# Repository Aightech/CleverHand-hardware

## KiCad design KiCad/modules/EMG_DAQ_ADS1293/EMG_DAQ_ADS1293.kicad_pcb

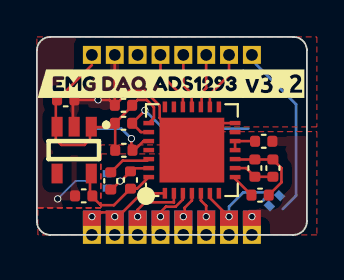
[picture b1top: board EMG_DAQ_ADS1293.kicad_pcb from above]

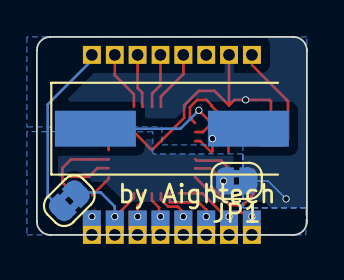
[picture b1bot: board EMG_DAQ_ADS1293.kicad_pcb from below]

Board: 4 copper layers, 15.0 x 11.0 mm, 34 parts (3 on the bottom side), 22 nets.

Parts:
C1, C5, C7: 100nF; C_0402_1005Metric
C2, C8, C9: 1uF; C_0402_1005Metric
C3, C4: 22pF; C_0402_1005Metric
C6: 1nF; C_0402_1005Metric
J1, J2, J3, J4, J5, J6, J7, J8, J9, J10, J11, J12, J13, J14, J15, J16: Conn_01x01_Pin; PinHeader_1x01_P1.27mm_Vertical
JP1, JP2: SolderJumper_2_Bridged; SolderJumper-2_P1.3mm_Bridged2Bar_RoundedPad1.0x1.5mm
R1: 10K; C_0402_1005Metric
R2: 10M; C_0402_1005Metric
U1: ADS1293CISQE-NOPB; ADS1293CISQE
U2: AP2112K-3.3TRG1; SOT-25-5_L2.9-W1.6-P0.95-LS2.8-BL
Y1: Crystal; Crystal_SMD_HC49-SD
kibuzzard-66CB9060: G***; kibuzzard-66CB9060
kibuzzard-658D7E24: G***; kibuzzard-658D7E24

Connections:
+3.3V: C3.1, C4.1, C5.1, C9.1, J13.1, U1.22 (VDDIO), U2.1 (VIN), U2.3 (EN)
+3.3VA: C1.1, C8.1, U1.28 (VDD), U2.5 (VOUT)
/CMOUT: R1.2, U1.8 (CMOUT)
/CSB: J12.1, U1.16 (CSB)
/PICO: J10.1, U1.18 (SDI)
/POCI: J9.1, U1.19 (SDO)
/RLDINV: C6.1, R1.1, R2.1, U1.10 (RLDINV)
/RLDOUT: C6.2, R2.2, U1.9 (RLDOUT)
/RLDREF: C7.1, U1.11 (RLDIN), U1.12 (RLDREF)
/SCLK: J11.1, U1.17 (SCLK)
/cvref: C2.1, U1.26 (CVREF)
/extRef: J7.1, JP2.1 (A)
/in1: J2.1, J3.1, U1.1 (IN1)
/in2: J4.1, U1.2 (IN2)
/in3: J5.1, U1.3 (IN3)
/in4: J6.1, U1.4 (IN4)
/in5: J8.1, U1.5 (IN5)
/in6: J15.1, JP2.2 (B), U1.6 (IN6)
GND: C5.2, C8.2, C9.2, J14.1, JP1.1 (A), U1.14 (VSSIO), U1.29 (EPAD), U2.2 (GND)
GNDA: C1.2, C2.2, C7.2, J16.1, JP1.2 (B), U1.27 (VSS)
XTAL1: C4.2, U1.23 (XTAL1), Y1.1
XTAL2: C3.2, U1.24 (XTAL2), Y1.2

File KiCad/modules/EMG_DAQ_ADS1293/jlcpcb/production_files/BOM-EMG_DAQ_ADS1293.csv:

Comment,Designator,Footprint,LCSC
10M,R2,C_0402_1005Metric,C102764
1nF,C6,C_0402_1005Metric,C1523
100nF,"C1,C5,C7",C_0402_1005Metric,C1525
22pF,"C3,C4",C_0402_1005Metric,C1555
ADS1293CISQE-NOPB,U1,ADS1293CISQE,C181260
10K,R1,C_0402_1005Metric,C25744
AP2112K-3.3TRG1,U2,SOT-25-5_L2.9-W1.6-P0.95-LS2.8-BL,C51118
1uF,"C2,C8,C9",C_0402_1005Metric,C52923
Crystal,Y1,Crystal_SMD_HC49-SD,C74858
Conn_01x01_Pin,J1,PinHeader_1x01_P1.27mm_Vertical,
Conn_01x01_Pin,J9,PinHeader_1x01_P1.27mm_Vertical,
Conn_01x01_Pin,J7,PinHeader_1x01_P1.27mm_Vertical,
Conn_01x01_Pin,J10,PinHeader_1x01_P1.27mm_Vertical,
Conn_01x01_Pin,J14,PinHeader_1x01_P1.27mm_Vertical,
Conn_01x01_Pin,J12,PinHeader_1x01_P1.27mm_Vertical,
Conn_01x01_Pin,J11,PinHeader_1x01_P1.27mm_Vertical,
Conn_01x01_Pin,J13,PinHeader_1x01_P1.27mm_Vertical,
SolderJumper_2_Bridged,JP2,SolderJumper-2_P1.3mm_Bridged2Bar_RoundedPad1.0x1.5mm,
SolderJumper_2_Bridged,JP1,SolderJumper-2_P1.3mm_Bridged2Bar_RoundedPad1.0x1.5mm,

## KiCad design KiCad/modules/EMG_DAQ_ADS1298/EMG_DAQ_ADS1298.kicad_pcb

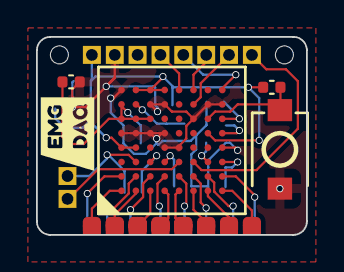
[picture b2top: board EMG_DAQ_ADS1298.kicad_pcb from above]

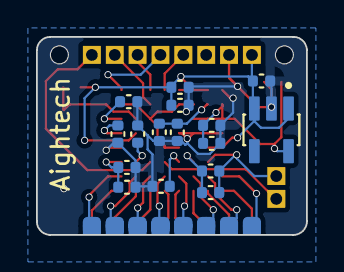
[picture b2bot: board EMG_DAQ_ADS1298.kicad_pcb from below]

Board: 4 copper layers, 15.0 x 11.0 mm, 47 parts (24 on the bottom side), 34 nets.

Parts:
C1, C2, C3, C5, C11, C12: 1uF; C_0402_1005Metric
C4, C6, C9, C14: 100nF; C_0402_1005Metric
C7: 1.5nF; C_0402_1005Metric
C8, C13: 10uF; C_0402_1005Metric
C10: 1nF; C_0402_1005Metric
C15: 22uF; C_0402_1005Metric
J1, J2, J3, J4, J5, J6, J7, J8, J25, J26: Conn_01x01_Pin; PinHeader_1x01_P1.27mm_Vertical
J9, J10, J11, J12, J13, J14, J15, J16, J17, J18, J19, J20, J21, J22, J23, J24: Conn_01x01_Pin; SolderWirePad_1x01_SMD_1x2mm
R1: 1M; C_0402_1005Metric
R2: 10K; C_0402_1005Metric
SW1: TS-1088R-02026; SW-SMD_L3.9-W3.0-P4.45
U1: AP2112K-3.3TRG1; SOT95P285X140-5N
U2: ADS1298CZXGT; NFBGA-64_L8.0-W8.0-R8-C8-P0.80-TL
kibuzzard-6569F40D: G***; kibuzzard-6569F40D

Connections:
+3.3V: C1.1, C3.2, C4.2, J1.1, R2.2, U1.1 (VIN), U1.3 (EN), U2.A4 (AVDD), U2.B4 (AVDD), U2.B8 (CLKSEL), U2.C8 (DVDD), U2.D8 (DVDD), U2.G5 (~PWDN)
+3.3VA: C2.1, C8.1, C9.1, U1.5 (VOUT), U2.A6 (AVDD), U2.A7 (AVDD1), U2.B6 (AVDD), U2.C6 (AVDD)
/BIAS_INV: C7.2, R1.1, U2.C3 (RLDINV)
/BIAS_OUT: C7.1, J26.1, R1.2, U2.B3 (RLDOUT)
/CSB: J7.1, U2.F7 (CS)
/MISO: J4.1, U2.E8 (DOUT)
/MOSI: J5.1, U2.H8 (DIN)
/RESET: R2.1, SW1.1, U2.G6 (~RESET)
/Refp: J25.1, U2.E3 (TESTP_PACE_OUT1)
/SCLK: J6.1, U2.F8 (SCLK)
/VCAP1: C15.1, U2.H5 (VCAP1)
/VCAP2: C12.1, U2.H6 (VCAP2)
/VCAP3: C5.1, C6.1, U2.B7 (VCAP3)
/VCAP4: C11.1, U2.G3 (VCAP4)
/VREFP: C13.1, C14.1, U2.H3 (VREFP)
/WCT: C10.1, U2.D3 (WCT)
/extRef: J8.1, U2.F3 (TESTN_PACE_OUT2)
/in1+: J16.1, U2.H1 (IN1P)
/in1-: J24.1, U2.H2 (IN1N)
/in2+: J15.1, U2.G1 (IN2P)
/in2-: J23.1, U2.G2 (IN2N)
/in3+: J14.1, U2.F1 (IN3P)
/in3-: J22.1, U2.F2 (IN3N)
/in4+: J13.1, U2.E1 (IN4P)
/in4-: J21.1, U2.E2 (IN4N)
/in5+: J12.1, U2.D1 (IN5P)
/in5-: J20.1, U2.D2 (IN5N)
/in6+: J11.1, U2.C1 (IN6P)
/in6-: J19.1, U2.C2 (IN6N)
/in7+: J10.1, U2.B1 (IN7P)
/in7-: J18.1, U2.B2 (IN7N)
/in8+: J9.1, U2.A1 (IN8P)
/in8-: J17.1, U2.A2 (IN8N)
GND: C1.2, C2.2, C3.1, C4.1, C5.2, C6.2, C8.2, C9.2, C10.2, C11.2, C12.2, C13.2, C14.2, C15.2, J2.1, SW1.2, U1.2 (GND), U2.A5 (AVSS), U2.A8 (AVSS1), U2.B5 (AVSS), U2.C5 (AVSS), U2.C7 (DGND), U2.D4 (AVSS), U2.D5 (AVSS), U2.D7 (DGND), U2.E4 (RESV1), U2.F6 (DAISY_IN), U2.G7 (START), U2.H4 (VREFN), U2.H7 (DGND)

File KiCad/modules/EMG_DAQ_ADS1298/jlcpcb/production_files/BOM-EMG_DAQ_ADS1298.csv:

Comment,Designator,Footprint,LCSC
TS-1088R-02026,SW1,SW-SMD_L3.9-W3.0-P4.45,C455280
ADS1298CZXGT,U2,NFBGA-64_L8.0-W8.0-R8-C8-P0.80-TL,C882732
Conn_01x01_Pin,J1,PinHeader_1x01_P1.27mm_Vertical,
Conn_01x01_Pin,J5,PinHeader_1x01_P1.27mm_Vertical,
Conn_01x01_Pin,J4,PinHeader_1x01_P1.27mm_Vertical,
10K,R2,C_0402_1005Metric,
Conn_01x01_Pin,J8,PinHeader_1x01_P1.27mm_Vertical,
Conn_01x01_Pin,J7,PinHeader_1x01_P1.27mm_Vertical,
Conn_01x01_Pin,J25,PinHeader_1x01_P1.27mm_Vertical,
Conn_01x01_Pin,J26,PinHeader_1x01_P1.27mm_Vertical,
Conn_01x01_Pin,J2,PinHeader_1x01_P1.27mm_Vertical,
Conn_01x01_Pin,J6,PinHeader_1x01_P1.27mm_Vertical,
Conn_01x01_Pin,J3,PinHeader_1x01_P1.27mm_Vertical,
1uF,C2,C_0402_1005Metric,
1uF,C11,C_0402_1005Metric,
10uF,C13,C_0402_1005Metric,
100nF,C14,C_0402_1005Metric,
1uF,C1,C_0402_1005Metric,
1uF,C3,C_0402_1005Metric,
1nF,C10,C_0402_1005Metric,
AP2112K-3.3TRG1,U1,SOT95P285X140-5N,
1uF,C5,C_0402_1005Metric,
1.5nF,C7,C_0402_1005Metric,
1M,R1,C_0402_1005Metric,
100nF,C4,C_0402_1005Metric,
10uF,C8,C_0402_1005Metric,
22uF,C15,C_0402_1005Metric,
100nF,C9,C_0402_1005Metric,
1uF,C12,C_0402_1005Metric,
100nF,C6,C_0402_1005Metric,

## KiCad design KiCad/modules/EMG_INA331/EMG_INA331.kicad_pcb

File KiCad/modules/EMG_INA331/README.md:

# EMG INA331 Module
This module is a data acquisition module that embeds the INA331 and a LIS3DH accelerometer. The INA331 is responsible for acquiring the EMG signals from the electrodes while the LIS3DH is responsible for acquiring the accelerometer signals and converting the EMG signals to digital signals.

## Electrical Schematic

## PCB Layout

## 3D Model

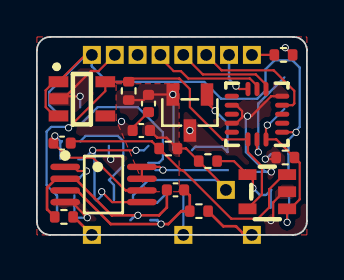
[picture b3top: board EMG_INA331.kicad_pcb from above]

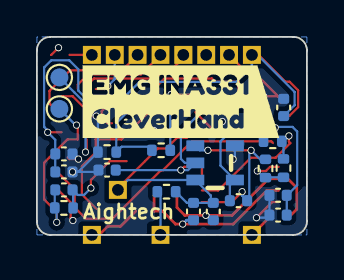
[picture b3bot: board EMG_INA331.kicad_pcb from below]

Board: 4 copper layers, 15.0 x 11.0 mm, 50 parts (22 on the bottom side), 23 nets.

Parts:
C1: 10uF; C_0402_1005Metric
C2, C9, C12: 100nF; C_0402_1005Metric
C3: 10nF; C_0402_1005Metric
C4, C5: 100pF; C_0402_1005Metric
C6, C7, C8, C10, C11, C13: 1uF; C_0402_1005Metric
C14: 100n; C_0402_1005Metric
C15: 1u; C_0402_1005Metric
J1, J2, J3, J4, J5, J6, J7, J8, J9, J10, J11, J12: Conn_01x01_Pin; PinHeader_1x01_P1.27mm_Vertical
R1: 2k; R_0402_1005Metric
R2, R6, R7: 10k; R_0402_1005Metric
R3: 330; R_0402_1005Metric
R4, R5: 4k; R_0402_1005Metric
R8, R11: 100k; R_0402_1005Metric
R9: 1M; R_0402_1005Metric
R10, R12: 1k; R_0402_1005Metric
R13, R14: 0; R_0402_1005Metric
TP1, TP2: TestPoint; TestPoint_Pad_D1.0mm
U1: INA331IDGKR; VSSOP-8_L3.0-W3.0-P0.65-LS5.0-BL
U2, U4: OPA333; SOT-23-5_L2.9-W1.6-P0.95-LS2.8-BR
U3: AP2112K-3.3TRG1; SOT-25-5_L2.9-W1.6-P0.95-LS2.8-BL
U5: CJ432; SOT-23-3_L2.9-W1.3-P1.90-LS2.4-BR
U6: LIS3DHTR; LGA-16_L3.0-W3.0-P0.50-TL
kibuzzard-6606B2BA: G***; kibuzzard-6606B2BA

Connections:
+3.3V: C6.1, C14.1, C15.1, J1.1, U3.1 (VIN), U3.3 (EN), U6.1 (VDD_IO)
+3.3VA: C7.2, C9.1, C11.1, C12.1, R3.1, U1.7 (V+), U1.8 (Shutdown), U2.2 (V-), U3.5 (VOUT), U4.5 (V+), U6.14 (VDD)
/ADC2: TP2.1, U6.15 (ADC2)
/CSB: J7.1, U6.8 (CS)
/IN+: C3.1, C4.1, R4.2, U1.2 (VIN-)
/IN-: C3.2, C5.2, R5.2, U1.3 (VIN+)
/OUT1: C13.2, R11.2, R12.1, TP1.1, U4.1 (OUT), U6.16 (ADC1)
/OUT_INA: C10.1, R7.2, R8.2, U1.6 (VOUT)
/PICO: J5.1, U6.6 (SDA/SDI/SDO)
/POCI: J4.1, U6.7 (SDO/SA0)
/PROB+: J10.1, R4.1
/PROB-: J9.1, R5.1
/REF: C8.1, R6.1, U1.5 (REF), U2.1 (OUT)
/SCLK: J6.1, U6.4 (SCL/SPC)
/extRef: J8.1, R14.1
GND: C1.2, C2.2, C6.2, C7.1, C9.2, C11.2, C12.2, C14.2, C15.2, J2.1, R2.2, R12.2, U1.4 (V-), U2.5 (V+), U3.2 (GND), U4.2 (V-), U5.3 (A), U6.5 (GND), U6.10 (RES), U6.12 (GND)
unnamed: J11.1, R13.1
unnamed: R6.2, R7.1, U1.1 (RG)
unnamed: C8.2, R8.1, U2.4 (-IN)
unnamed: C10.2, R9.1, U4.3 (+IN)
unnamed: C13.1, R10.2, R11.1, U4.4 (-IN)
unnamed: R1.2, R2.1, U5.1 (R)
Vref: C1.1, C2.1, C4.2, C5.1, J12.1, R1.1, R3.2, R9.2, R10.1, R13.2, R14.2, U2.3 (+IN), U5.2 (K)

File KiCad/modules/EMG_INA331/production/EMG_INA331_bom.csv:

"Reference","Value","Footprint","DNP","LCSC"
"C1","10uF","Capacitor_SMD:C_0402_1005Metric","",""
"C2","100nF","Capacitor_SMD:C_0402_1005Metric","",""
"C3","10nF","Capacitor_SMD:C_0402_1005Metric","",""
"C4","100pF","Capacitor_SMD:C_0402_1005Metric","",""
"C5","100pF","Capacitor_SMD:C_0402_1005Metric","",""
"C6","1uF","Capacitor_SMD:C_0402_1005Metric","",""
"C7","1uF","Capacitor_SMD:C_0402_1005Metric","",""
"C8","1uF","Capacitor_SMD:C_0402_1005Metric","",""
"C9","100nF","Capacitor_SMD:C_0402_1005Metric","",""
"C10","1uF","Capacitor_SMD:C_0402_1005Metric","",""
"C11","1uF","Capacitor_SMD:C_0402_1005Metric","",""
"C12","100nF","Capacitor_SMD:C_0402_1005Metric","",""
"C13","1uF","Capacitor_SMD:C_0402_1005Metric","",""
"C14","100n","Capacitor_SMD:C_0402_1005Metric","",""
"C15","1u","Capacitor_SMD:C_0402_1005Metric","",""
"J1","Conn_01x01_Pin","00_custom-footprints:PinHeader_1x01_P1.27mm_Vertical","",""
"J2","Conn_01x01_Pin","00_custom-footprints:PinHeader_1x01_P1.27mm_Vertical","",""
"J3","Conn_01x01_Pin","00_custom-footprints:PinHeader_1x01_P1.27mm_Vertical","",""
"J4","Conn_01x01_Pin","00_custom-footprints:PinHeader_1x01_P1.27mm_Vertical","",""
"J5","Conn_01x01_Pin","00_custom-footprints:PinHeader_1x01_P1.27mm_Vertical","",""
"J6","Conn_01x01_Pin","00_custom-footprints:PinHeader_1x01_P1.27mm_Vertical","",""
"J7","Conn_01x01_Pin","00_custom-footprints:PinHeader_1x01_P1.27mm_Vertical","",""
"J8","Conn_01x01_Pin","00_custom-footprints:PinHeader_1x01_P1.27mm_Vertical","",""
"R1","2k","Resistor_SMD:R_0402_1005Metric","",""
"R2","10k","Resistor_SMD:R_0402_1005Metric","",""
"R3","330","Resistor_SMD:R_0402_1005Metric","",""
"R4","4k","Resistor_SMD:R_0402_1005Metric","",""
"R5","4k","Resistor_SMD:R_0402_1005Metric","",""
"R6","10k","Resistor_SMD:R_0402_1005Metric","",""
"R7","10k","Resistor_SMD:R_0402_1005Metric","",""
"R8","100k","Resistor_SMD:R_0402_1005Metric","",""
"R9","1M","Resistor_SMD:R_0402_1005Metric","",""
"R10","1k","Resistor_SMD:R_0402_1005Metric","",""
"R11","100k","Resistor_SMD:R_0402_1005Metric","",""
"R12","1k","Resistor_SMD:R_0402_1005Metric","",""
"TP1","TestPoint","00_custom-footprints:TestPoint_Pad_D1.0mm","",""
"TP2","TestPoint","00_custom-footprints:TestPoint_Pad_D1.0mm","",""
"TP3","TestPoint","00_custom-footprints:TestPoint_Pad_D1.0mm","",""
"U1","INA350ABSIDSGR","00_lcsc:WSON-8_L2.0-W2.0-P0.50-TL-EP","","C4370677"
"U2","OPA333","00_lcsc:SOT-23-5_L2.9-W1.6-P0.95-LS2.8-BR","","C3007938"
"U3","AP2112K-3.3TRG1","00_lcsc:SOT-25-5_L2.9-W1.6-P0.95-LS2.8-BL","","C51118"
"U4","OPA333","00_lcsc:SOT-23-5_L2.9-W1.6-P0.95-LS2.8-BR","","C3007938"
"U5","CJ432","00_lcsc:SOT-23-3_L2.9-W1.3-P1.90-LS2.4-BR","","C2910208"
"U6","LIS3DHTR","00_lcsc:LGA-16_L3.0-W3.0-P0.50-TL","","C15134"

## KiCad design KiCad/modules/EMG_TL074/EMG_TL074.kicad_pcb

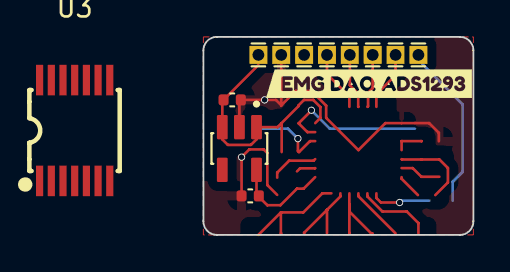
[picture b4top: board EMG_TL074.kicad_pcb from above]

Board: 4 copper layers, 15.0 x 11.0 mm, 13 parts (0 on the bottom side), 3 nets.

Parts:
C8, C9: 1uF; C_0402_1005Metric
J1, J7, J9, J10, J11, J12, J13, J14: Conn_01x01_Pin; PinHeader_1x01_P1.27mm_Vertical
U2: AP2112K-3.3TRG1; SOT95P285X140-5N
U3: TL074HIPWR; TSSOP-14_L5.0-W4.4-P0.65-LS6.4-BL
kibuzzard-658D7E24: G***; kibuzzard-658D7E24

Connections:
+3.3V: C9.1, J13.1, U2.1 (VIN), U2.3 (EN)
+3.3VA: C8.1, U2.5 (VOUT)
GND: C8.2, C9.2, J14.1, U2.2 (GND)

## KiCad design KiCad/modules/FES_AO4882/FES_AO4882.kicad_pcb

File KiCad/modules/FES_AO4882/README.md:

# FES AO4882 Module
This module is a electrical stimulation module that embeds 2 AO4882 MOSFETs. It is responsible for generating the electrical stimulation signals that will be sent to the electrodes. 

## Electrical Schematic

## PCB Layout

## 3D Model

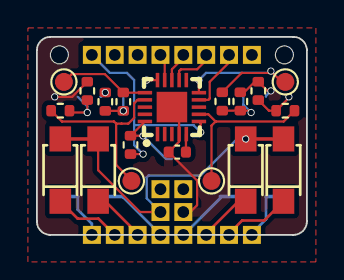
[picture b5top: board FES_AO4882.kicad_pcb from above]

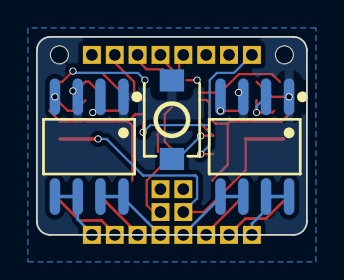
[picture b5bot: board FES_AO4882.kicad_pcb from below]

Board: 4 copper layers, 15.0 x 11.0 mm, 42 parts (3 on the bottom side), 26 nets.

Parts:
C1: 4.7uF; C_0402_1005Metric
J1, J2, J3, J4, J5, J6, J7, J8, J11, J12, J13, J14, J15, J16, J17, J20, J21, J22, J23, J24: Conn_01x01_Pin; PinHeader_1x01_P1.27mm_Vertical
J9, J10, J18, J19: Conn_01x01_Pin; TestPoint_Pad_D1.0mm
Q1, Q2: AO4882_C3040598; SOIC-8_L4.9-W3.9-P1.27-LS6.0-BL
R1, R3, R6, R7: 1k; R_0402_1005Metric
R2: 10K; R_0402_1005Metric
R4, R5, R8, R9: 2k; R_0402_1005Metric
SW1: TS-1088R-02026; SW-SMD_L3.9-W3.0-P4.45
U1, U2, U3, U5: DS12W-MS; SOD-123FL_L2.7-W1.8-LS3.8-RD
U4: HC32L110C6UA-SFN20TR; WQFN-20_L3.0-W3.0-P0.40-BL-EP

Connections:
+3.3V: J1.1, R2.2, U4.6 (AVCC)
/FES1in: J11.1, U3.1 (C)
/FES1out: J12.1, Q1.7 (D1), Q1.8 (D1)
/FES2in: J13.1, U2.1 (C)
/FES2out: J14.1, Q1.5 (D2), Q1.6 (D2)
/FES3in: J20.1, U5.1 (C)
/FES3out: J21.1, Q2.7 (D1), Q2.8 (D1)
/FES4in: J22.1, U1.1 (C)
/FES4out: J23.1, Q2.5 (D2), Q2.6 (D2)
/GPIO: R2.1, SW1.1, U4.20 (GPIO)
/PICO_ARM: J5.1, U4.13 (SPI_PICO)
/PWM1: J9.1, R1.1, U4.10 (PCA_CH0)
/PWM1_: Q1.2 (G1), R1.2, R4.2
/PWM2: J10.1, R3.1, U4.7 (PCA_CH3)
/PWM2_: Q1.4 (G2), R3.2, R5.2
/PWM3: J18.1, R6.1, U4.17 (PCA_CH1)
/PWM3_: Q2.2 (G1), R6.2, R8.2
/PWM4: J19.1, R7.1, U4.16 (PCA_CH2)
/PWM4_: Q2.4 (G2), R7.2, R9.2
/SCLK_ARM: J6.1, U4.12 (SPI_SCK)
/SPICS_ARM: J7.1, U4.9 (SPI_CS)
/SWCLK: J15.1, U4.15 (SWCLK)
/SWDIO/POCI_ARM: J4.1, J16.1, U4.14 (SWDIO)
/Vcap: C1.2, U4.5 (Vcap)
GND: C1.1, J2.1, J17.1, Q1.1 (S1), Q1.3 (S2), Q2.1 (S1), Q2.3 (S2), R4.1, R5.1, R8.1, R9.1, SW1.2, U4.4 (AVSS), U4.21 (EPAD)
VCC: J24.1, U1.2 (A), U2.2 (A), U3.2 (A), U5.2 (A)

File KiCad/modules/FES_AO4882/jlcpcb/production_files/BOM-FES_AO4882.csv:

Comment,Designator,Footprint,LCSC
4.7uF,C1,C_0402_1005Metric,C23733
AO4882_C3040598,"Q1,Q2",SOIC-8_L4.9-W3.9-P1.27-LS6.0-BL,C3040598
TS-1088R-02026,SW1,SW-SMD_L3.9-W3.0-P4.45,C455280
HC32L110C6UA-SFN20TR,U4,WQFN-20_L3.0-W3.0-P0.40-BL-EP,C493490
DS12W-MS,"U1,U2,U3,U5",SOD-123FL_L2.7-W1.8-LS3.8-RD,C5120757
Conn_01x01_Pin,J24,PinHeader_1x01_P1.27mm_Vertical,
Conn_01x01_Pin,J17,PinHeader_1x01_P1.27mm_Vertical,
Conn_01x01_Pin,J16,PinHeader_1x01_P1.27mm_Vertical,
Conn_01x01_Pin,J15,PinHeader_1x01_P1.27mm_Vertical,
Conn_01x01_Pin,J23,PinHeader_1x01_P1.27mm_Vertical,
Conn_01x01_Pin,J22,PinHeader_1x01_P1.27mm_Vertical,
Conn_01x01_Pin,J21,PinHeader_1x01_P1.27mm_Vertical,
Conn_01x01_Pin,J20,PinHeader_1x01_P1.27mm_Vertical,
2k,R9,R_0402_1005Metric,
2k,R8,R_0402_1005Metric,
1k,R7,R_0402_1005Metric,
1k,R6,R_0402_1005Metric,
2k,R5,R_0402_1005Metric,
2k,R4,R_0402_1005Metric,
1k,R3,R_0402_1005Metric,
10K,R2,R_0402_1005Metric,
1k,R1,R_0402_1005Metric,
Conn_01x01_Pin,J19,TestPoint_Pad_D1.0mm,
Conn_01x01_Pin,J14,PinHeader_1x01_P1.27mm_Vertical,
Conn_01x01_Pin,J13,PinHeader_1x01_P1.27mm_Vertical,
Conn_01x01_Pin,J12,PinHeader_1x01_P1.27mm_Vertical,
Conn_01x01_Pin,J11,PinHeader_1x01_P1.27mm_Vertical,
Conn_01x01_Pin,J10,TestPoint_Pad_D1.0mm,
Conn_01x01_Pin,J18,TestPoint_Pad_D1.0mm,
Conn_01x01_Pin,J9,TestPoint_Pad_D1.0mm,
Conn_01x01_Pin,J1,PinHeader_1x01_P1.27mm_Vertical,
Conn_01x01_Pin,J5,PinHeader_1x01_P1.27mm_Vertical,
Conn_01x01_Pin,J4,PinHeader_1x01_P1.27mm_Vertical,
Conn_01x01_Pin,J8,PinHeader_1x01_P1.27mm_Vertical,
Conn_01x01_Pin,J7,PinHeader_1x01_P1.27mm_Vertical,
Conn_01x01_Pin,J2,PinHeader_1x01_P1.27mm_Vertical,
Conn_01x01_Pin,J6,PinHeader_1x01_P1.27mm_Vertical,
Conn_01x01_Pin,J3,PinHeader_1x01_P1.27mm_Vertical,

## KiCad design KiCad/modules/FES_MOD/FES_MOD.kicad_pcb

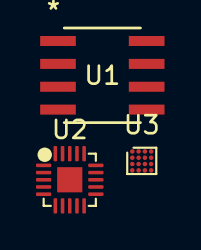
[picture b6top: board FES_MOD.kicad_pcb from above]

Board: 4 copper layers, 3 parts (0 on the bottom side), 3 nets, no tracks yet.

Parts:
U1: AO4882; SO-8_AOS
U2: HC32L110C6UA; QFN-20-1EP_3x3mm_P0.4mm_EP1.4x1.4mm
U3: HC32L110C6UA; CSP16_1.59x1.436mm_P0.35mm_JLCPCB

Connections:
GND: U1.1 (S2), U1.3 (S1)
unnamed: U1.7 (D2), U1.8 (D2)
unnamed: U1.5 (D1), U1.6 (D1)

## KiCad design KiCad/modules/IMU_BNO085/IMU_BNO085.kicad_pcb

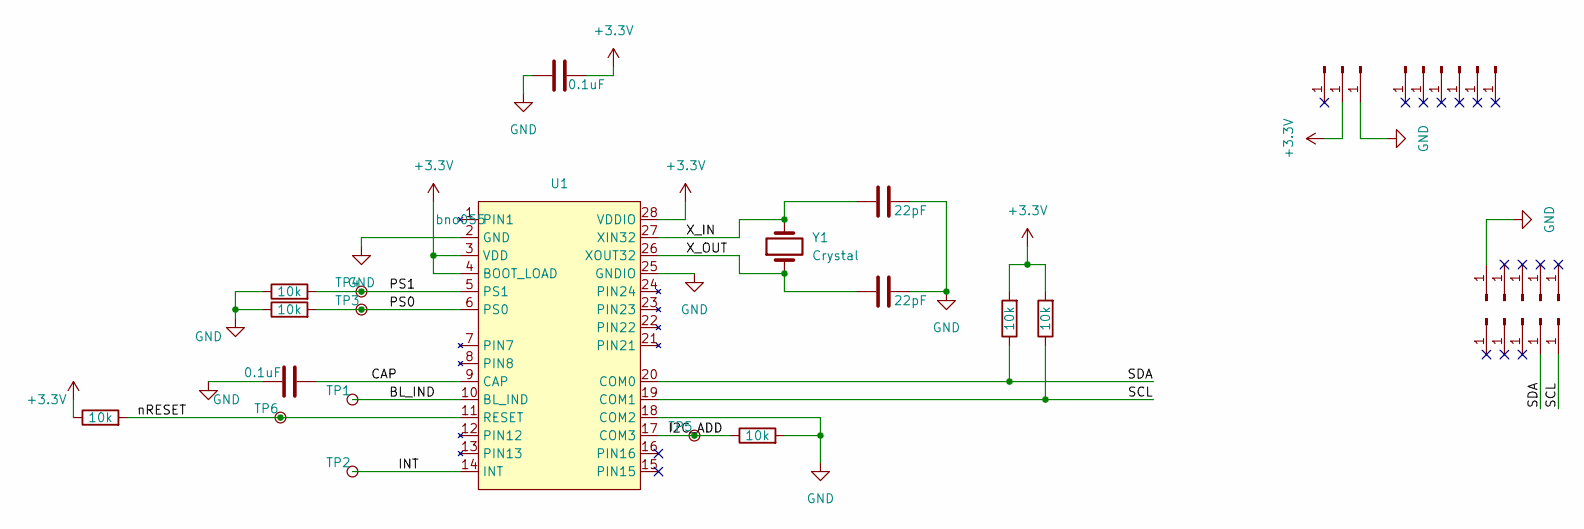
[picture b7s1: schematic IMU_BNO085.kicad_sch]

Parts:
C1, C2: 0.1uF; C_0402_1005Metric
C3, C4: 22pF; C_0402_1005Metric
J1, J2, J3, J4, J5, J6, J7, J8, J9, J10, J11, J12, J13, J14, J15, J16, J17, J18, J19: Conn_01x01_Pin; PinHeader_1x01_P1.27mm_Vertical
R1, R2, R3, R4, R5, R6: 10k; R_0402_1005Metric
TP1, TP2, TP3, TP4, TP5, TP6: TestPoint; TestPoint_Pad_D1.0mm
U1: bno055; LGA-28_5.2x3.8mm_BNO0055
Y1: Crystal; Crystal_SMD_3215-2Pin_3.2x1.5mm; LCSC C32346

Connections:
+3.3V: C1.2, J1.1, R4.2, R5.2, R6.1, U1.3 (VDD), U1.4 (BOOT_LOAD), U1.28 (VDDIO)
/BL_IND: TP1.1, U1.10 (BL_IND)
/CAP: C2.1, U1.9 (CAP)
/I2C_ADD: R1.1, TP5.1, U1.17 (COM3)
/INT: TP2.1, U1.14 (INT)
/PS0: R2.2, TP3.1, U1.6 (PS0)
/PS1: R3.2, TP4.1, U1.5 (PS1)
/SCL: J3.1, R5.1, U1.19 (COM1)
/SDA: J2.1, R4.1, U1.20 (COM0)
/X_IN: C3.1, U1.27 (XIN32), Y1.2
/X_OUT: C4.1, U1.26 (XOUT32), Y1.1
/nRESET: R6.2, TP6.1, U1.11 (RESET)
GND: C1.1, C2.2, C3.2, C4.2, J4.1, J19.1, R1.2, R2.1, R3.1, U1.2 (GND), U1.18 (COM2), U1.25 (GNDIO)

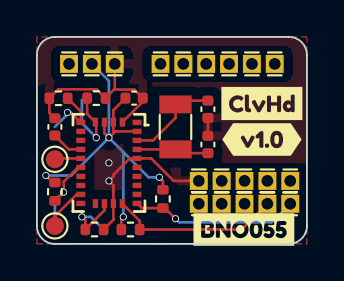
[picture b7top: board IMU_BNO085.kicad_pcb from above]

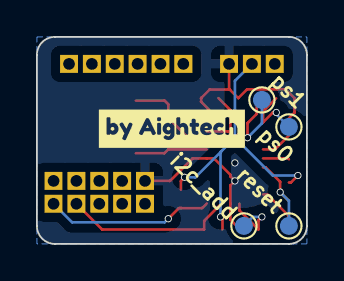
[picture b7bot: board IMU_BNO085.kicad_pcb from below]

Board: 4 copper layers, 15.0 x 11.5 mm, 41 parts (5 on the bottom side), 13 nets.

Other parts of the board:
kibuzzard-65916A49: G***; kibuzzard-65916A49
kibuzzard-65916AA3: G***; kibuzzard-65916AA3
kibuzzard-65916B8F: G***; kibuzzard-65916B8F
kibuzzard-65916B62: G***; kibuzzard-65916B62

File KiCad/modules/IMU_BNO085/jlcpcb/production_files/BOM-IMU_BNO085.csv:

Comment,Designator,Footprint,LCSC
22pF,"C3,C4",C_0402_1005Metric,C1555
0.1uF,"C1,C2",C_0402_1005Metric,C2167244
10k,"R1,R2,R3,R4,R5,R6",R_0402_1005Metric,C25744
Crystal,Y1,Crystal_SMD_3215-2Pin_3.2x1.5mm,C32346
bno055,U1,LGA-28_5.2x3.8mm_BNO0055,C93216
TestPoint,TP2,TestPoint_Pad_D1.0mm,
TestPoint,TP1,TestPoint_Pad_D1.0mm,
TestPoint,TP6,TestPoint_Pad_D1.0mm,
TestPoint,TP5,TestPoint_Pad_D1.0mm,
TestPoint,TP4,TestPoint_Pad_D1.0mm,
TestPoint,TP3,TestPoint_Pad_D1.0mm,
